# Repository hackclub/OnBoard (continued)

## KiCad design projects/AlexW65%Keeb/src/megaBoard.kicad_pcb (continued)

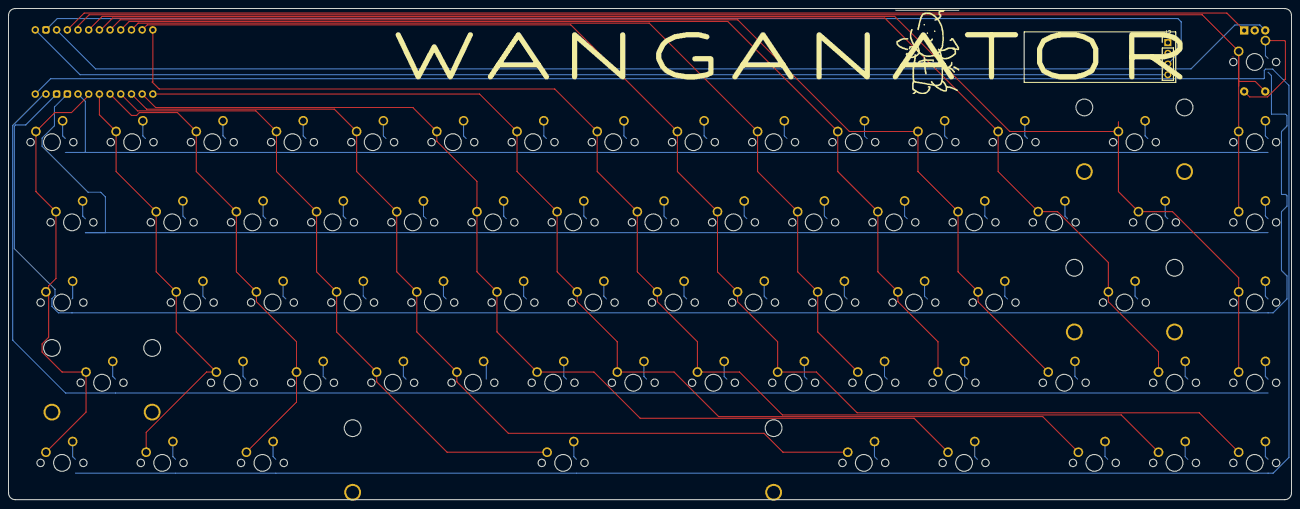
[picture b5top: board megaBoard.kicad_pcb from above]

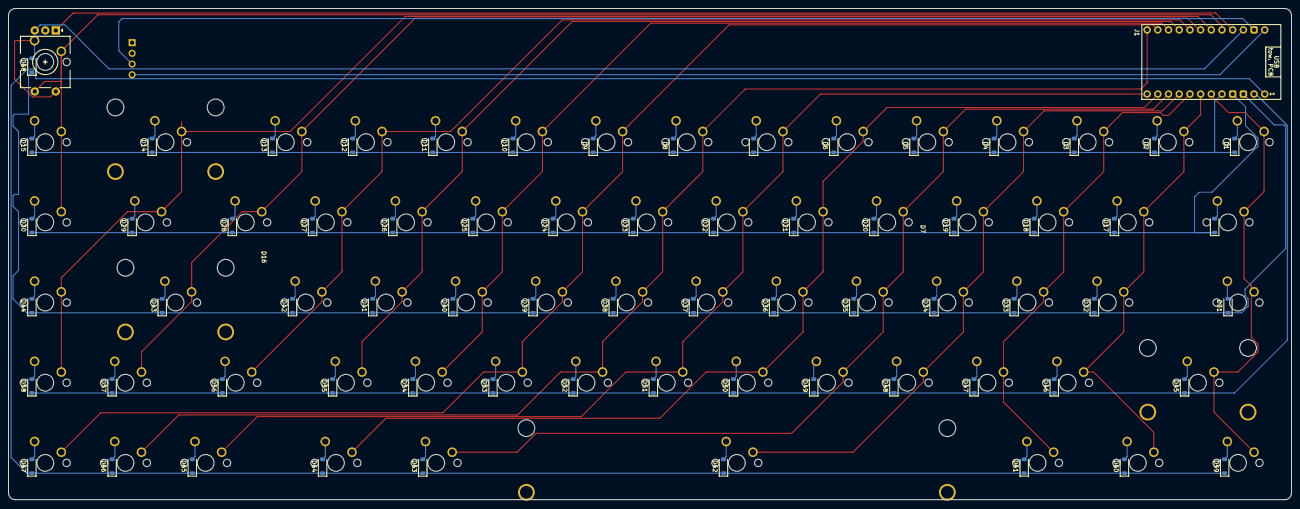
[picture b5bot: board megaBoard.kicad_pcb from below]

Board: 2 copper layers, 304.8 x 116.7 mm, 143 parts (70 on the bottom side), 93 nets.

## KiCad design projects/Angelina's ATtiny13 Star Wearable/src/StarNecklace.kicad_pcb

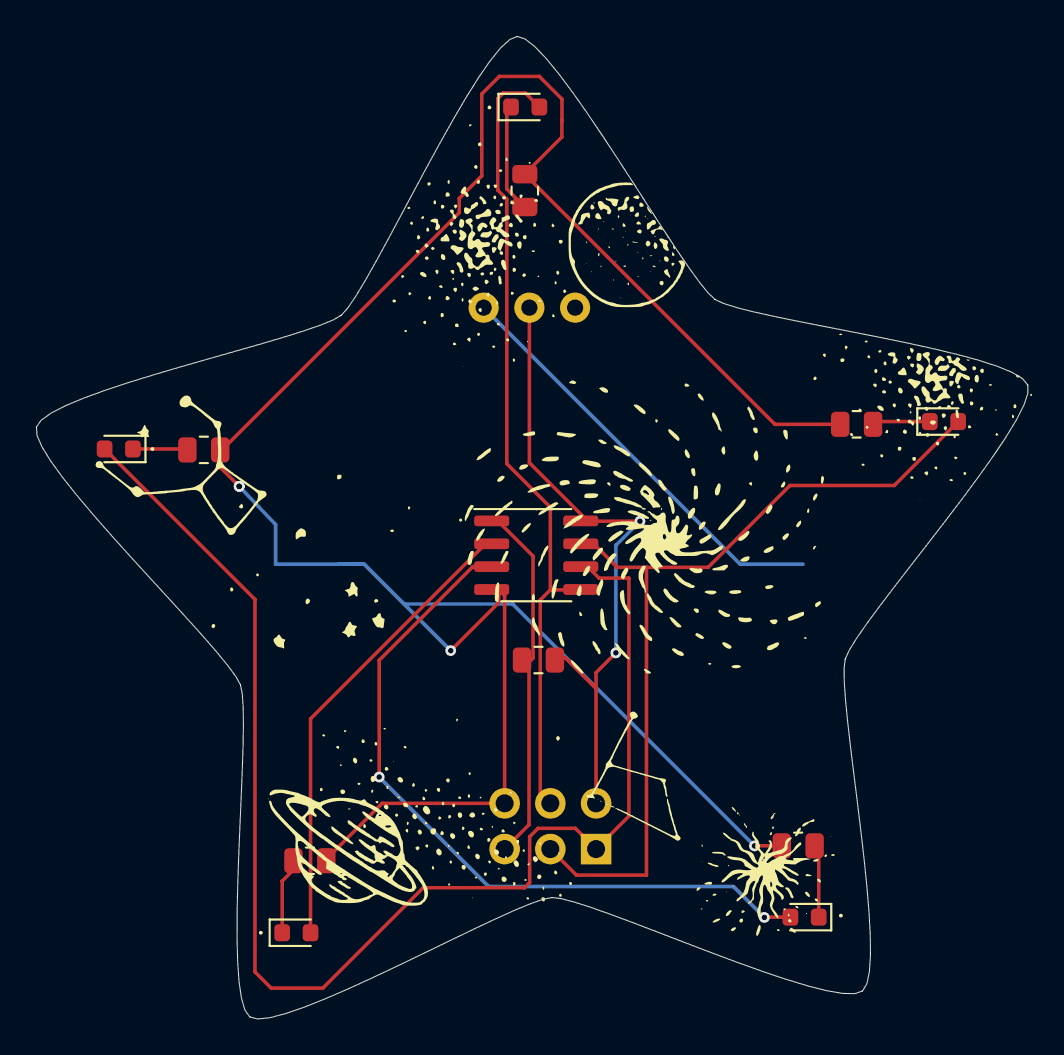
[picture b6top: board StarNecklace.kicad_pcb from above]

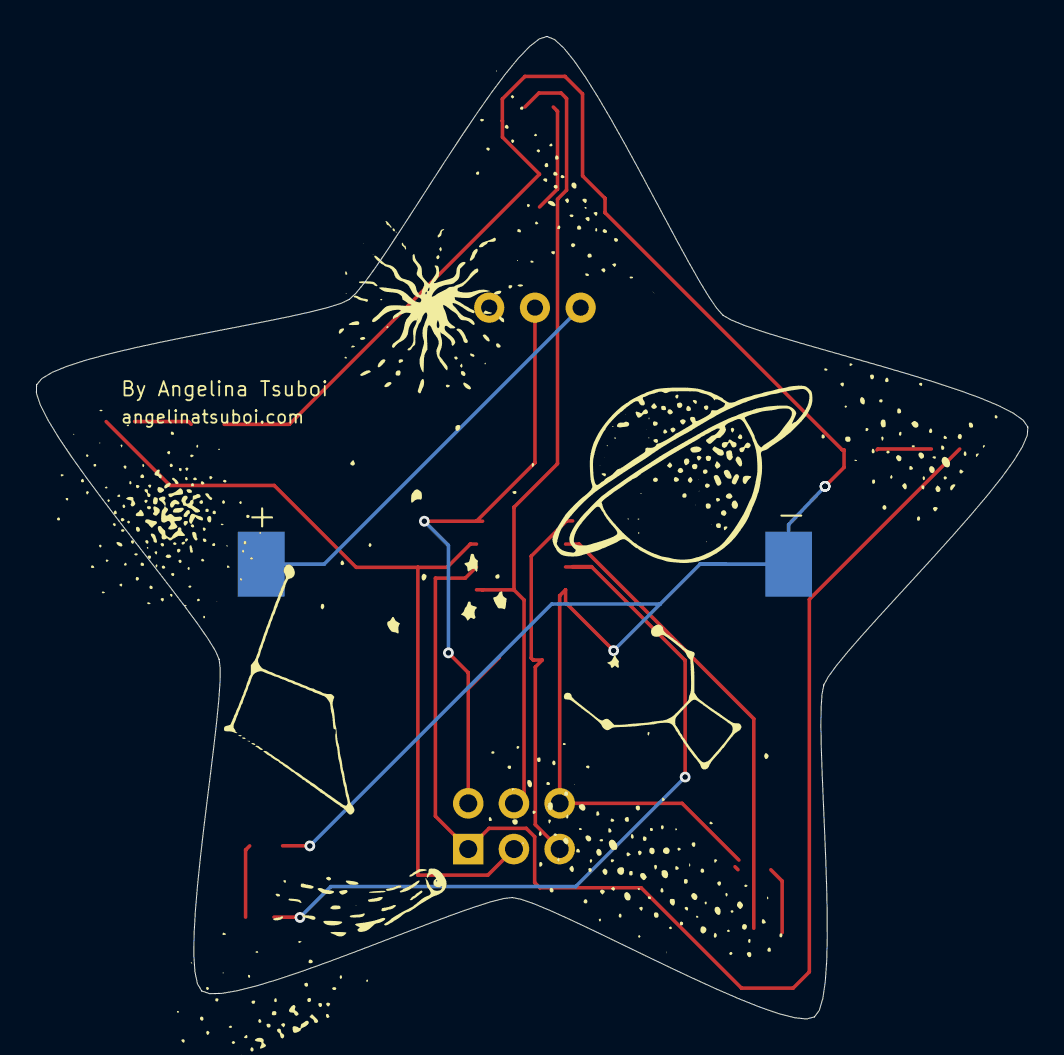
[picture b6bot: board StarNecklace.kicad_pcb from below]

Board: 2 copper layers, 55.1 x 54.6 mm, 15 parts (3 on the bottom side), 14 nets.

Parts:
BAT1: Coin Cell Holder 3V; BatteryHolder_Keystone_1060_1x2032
D1, D2, D3, D4, D5: LED; LED_0603_1608Metric
J1: Conn_02x03_Odd_Even; PinHeader_2x03_P2.54mm_Vertical
R1, R2, R3, R4, R5: 100; R_0805_2012Metric
R6: 4.7k; R_0805_2012Metric
SW1: SW_SPDT; Schiebeschalter_SS-12D00
U1: ATtiny13A; SOIC-8_3.9x4.9mm_P1.27mm

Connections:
GNDREF: BAT1.2 (-), J1.6, R1.2, R2.2, R3.2, R4.2, R5.2, U1.4 (GND)
MISO: D2.2 (A), J1.1, U1.6 (PB1)
MOSI: D1.2 (A), J1.4, U1.5 (PB0)
unnamed: BAT1.1 (+), SW1.3 (C)
unnamed: D1.1 (K), R1.1
unnamed: D2.1 (K), R2.1
unnamed: D3.1 (K), R3.1
unnamed: D4.1 (K), R4.1
unnamed: D5.1 (K), R5.1
PB3: D4.2 (A), U1.2 (PB3)
PB4: D5.2 (A), U1.3 (PB4)
RST: J1.5, R6.2, U1.1 (~RESET/PB5)
SCK: D3.2 (A), J1.3, U1.7 (PB2)
VCC: J1.2, R6.1, SW1.2 (B), U1.8 (VCC)

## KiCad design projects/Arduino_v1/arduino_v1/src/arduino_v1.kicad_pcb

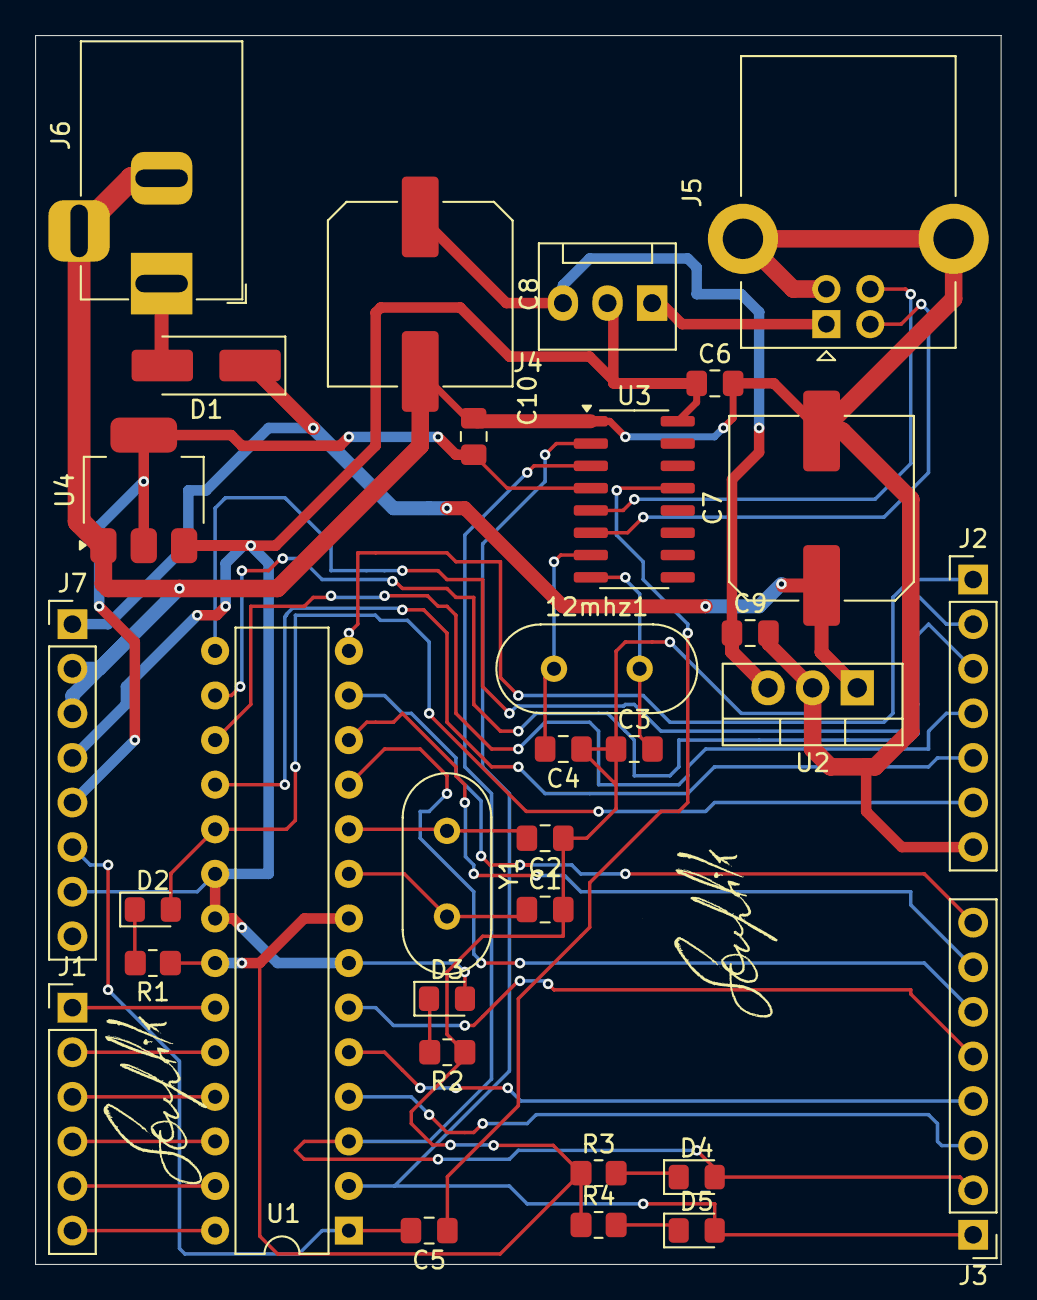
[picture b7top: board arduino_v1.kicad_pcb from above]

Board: 2 copper layers, 55.0 x 70.0 mm, 32 parts (0 on the bottom side), 39 nets.

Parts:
12mhz1: Crystal; Crystal_HC49-4H_Vertical
C1, C2, C3, C4: 22pf; C_0805_2012Metric_Pad1.18x1.45mm_HandSolder
C5, C6, C9, C10: 100nF; C_0805_2012Metric_Pad1.18x1.45mm_HandSolder
C7, C8: 100uF; C_Elec_10x10.2
D1: IN4007; D_SMA_Handsoldering
D2, D3, D4, D5: LED; LED_0805_2012Metric_Pad1.15x1.40mm_HandSolder
J1: Conn_01x06_Pin; PinHeader_1x06_P2.54mm_Vertical
J2: Conn_01x07_Pin; PinHeader_1x07_P2.54mm_Vertical
J3, J7: Conn_01x08_Pin; PinHeader_1x08_P2.54mm_Vertical
J4: Conn_01x03_Pin; FanPinHeader_1x03_P2.54mm_Vertical
J5: USB_B; USB_B_Lumberg_2411_02_Horizontal
J6: Barrel_Jack_Switch; BarrelJack_Horizontal
R1, R2, R3, R4: 330R; R_0805_2012Metric_Pad1.20x1.40mm_HandSolder
U1: ATmega328-P; DIP-28_W7.62mm
U2: LM7805_TO220; TO-220-3_Vertical
U3: CH340G; SOIC-16_3.9x9.9mm_P1.27mm
U4: AMS1117-3.3; SOT-223-3_TabPin2
Y1: Crystal; Crystal_HC49-4H_Vertical

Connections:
3.3V: C10.1, J7.5, U3.4 (V3), U4.2 (VO)
5V: C8.1, C9.1, J4.3, U2.3 (VO)
5VU: J4.1, J5.1 (VBUS)
A0: J1.1, U1.23 (PC0)
A1: J1.2, U1.24 (PC1)
A2: J1.3, U1.25 (PC2)
A3: J1.4, U1.26 (PC3)
A4: J1.5, U1.27 (PC4)
A5: J1.6, U1.28 (PC5)
D2: J3.3, U1.4 (PD2)
D3: J3.4, U1.5 (PD3)
D4: J3.5, U1.6 (PD4)
D5: J3.6, U1.11 (PD5)
D6: J3.7, U1.12 (PD6)
D7: J3.8, U1.13 (PD7)
D8: J2.1, U1.14 (PB0)
D9: J2.2, U1.15 (PB1)
D10: J2.3, U1.16 (PB2)
D11: J2.4, U1.17 (PB3)
D12: J2.5, U1.18 (PB4)
D13: D2.2 (A), J2.6, U1.19 (PB5)
GND: C1.2, C2.1, C3.1, C4.1, C6.2, C7.2, C8.2, C9.2, C10.2, J2.7, J5.4 (GND), J5.5 (Shield), J6.2, J6.3, J7.2, J7.3, R1.1, R2.1, R3.1, R4.1, U1.8 (GND), U1.22 (GND), U2.2 (GND), U3.1 (GND), U4.1 (GND)
unnamed: D1.2 (A), J6.1
unnamed: D2.1 (K), R1.2
unnamed: D3.1 (K), R2.2
unnamed: D4.1 (K), R3.2
unnamed: D5.1 (K), R4.2
unnamed: J5.3 (D+), U3.5 (UD+)
unnamed: J5.2 (D-), U3.6 (UD-)
unnamed: C1.1, U1.9 (XTAL1/PB6), Y1.2
unnamed: C2.2, U1.10 (XTAL2/PB7), Y1.1
unnamed: 12mhz1.1, C4.2, U3.7 (XI)
unnamed: 12mhz1.2, C3.2, U3.8 (XO)
unnamed: C5.1, U3.13 (~DTR)
RST: C5.2, J7.6, U1.1 (~RESET/PC6)
RXD: D5.2 (A), J3.1, U1.2 (PD0), U3.2 (TXD)
TXD: D4.2 (A), J3.2, U1.3 (PD1), U3.3 (RXD)
VCC: C6.1, D3.2 (A), J4.2, J7.4, J7.7, U1.7 (VCC), U1.20 (AVCC), U1.21 (AREF), U3.16 (VCC), U4.3 (VI)
VIN: C7.1, D1.1 (K), J7.1, U2.1 (VI)

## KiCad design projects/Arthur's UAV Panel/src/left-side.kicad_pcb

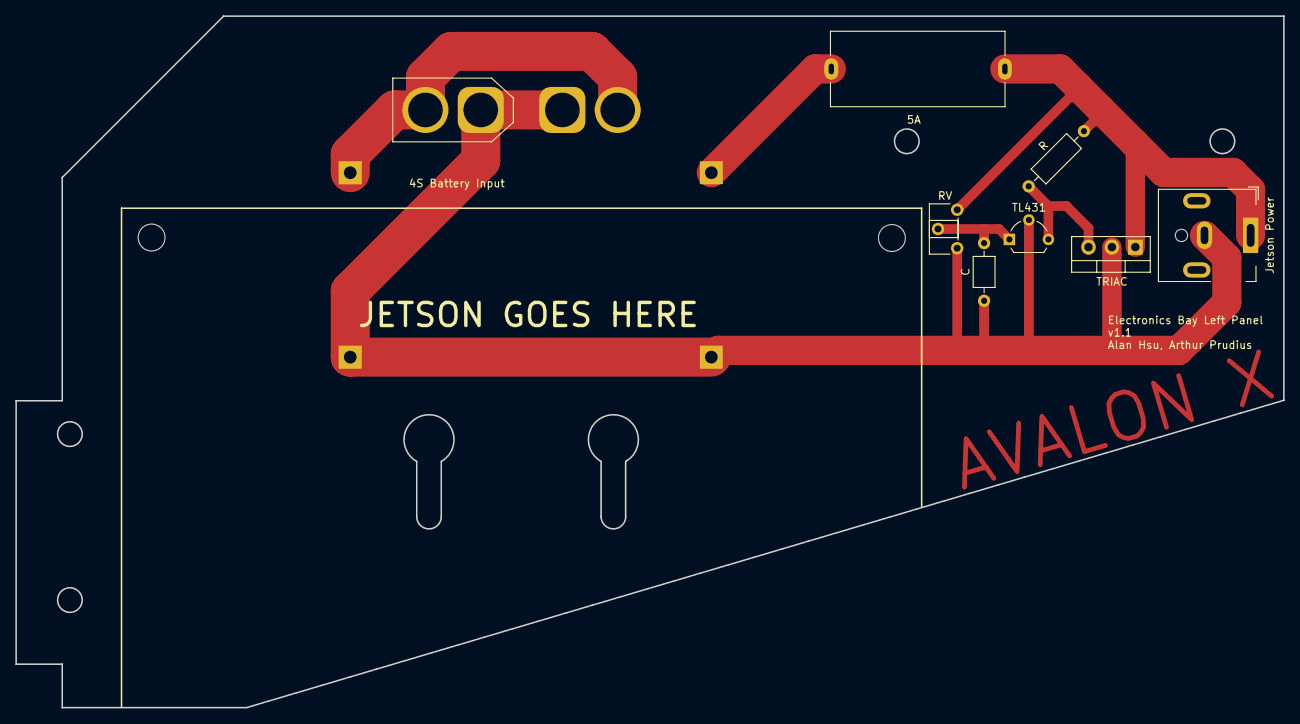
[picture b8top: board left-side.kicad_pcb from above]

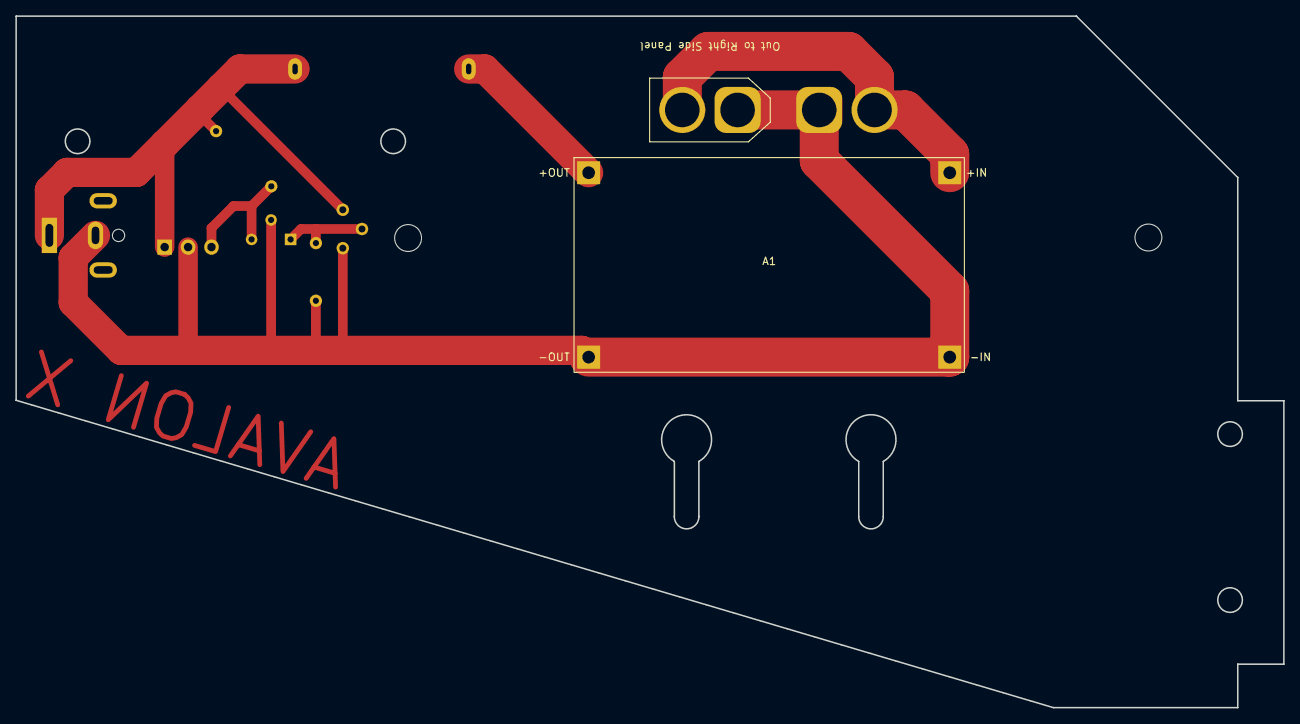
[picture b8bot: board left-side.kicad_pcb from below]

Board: 2 copper layers, 165.0 x 90.0 mm, 10 parts (2 on the bottom side), 3 nets.

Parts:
5A: Fuseholder_Cylinder-5x20mm_Schurter_0031_8201_Hor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; Fuseholder_Cylinder-5x20mm_Schurter_0031_8201_Horizontal_Op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
A1: Buck
C: C_Axial_L3.8mm_D2.6mm_P7.50mm_Horizontal
J1: XT60; AMASS_XT60-M_1x02_P7.20mm_Vertical
J2: XT60; AMASS_XT60-F_1x02_P7.20mm_Vertical
Jetson Power: BarrelJack_GCT_DCJ200-10-A_Horizontal
R: R_Axial_DIN0207_L6.3mm_D2.5mm_P10.16mm_Horizontal
RV: Potentiometer_ACP_CA6-H2,5_Horizontal
TL431: TO-92L_Wide
TRIAC: TO-220-3_Vertical

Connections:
+BATT: A1.4 (VOUT), J1.2, J2.2
GND: A1.2 (GND), A1.3 (GND), C.1, J1.1, J2.1, Jetson Power.2, RV.1, TL431.2, TRIAC.2
unnamed: 5A.1, 5A.2, A1.1 (VIN), Jetson Power.1, R.2, RV.3, TRIAC.1
